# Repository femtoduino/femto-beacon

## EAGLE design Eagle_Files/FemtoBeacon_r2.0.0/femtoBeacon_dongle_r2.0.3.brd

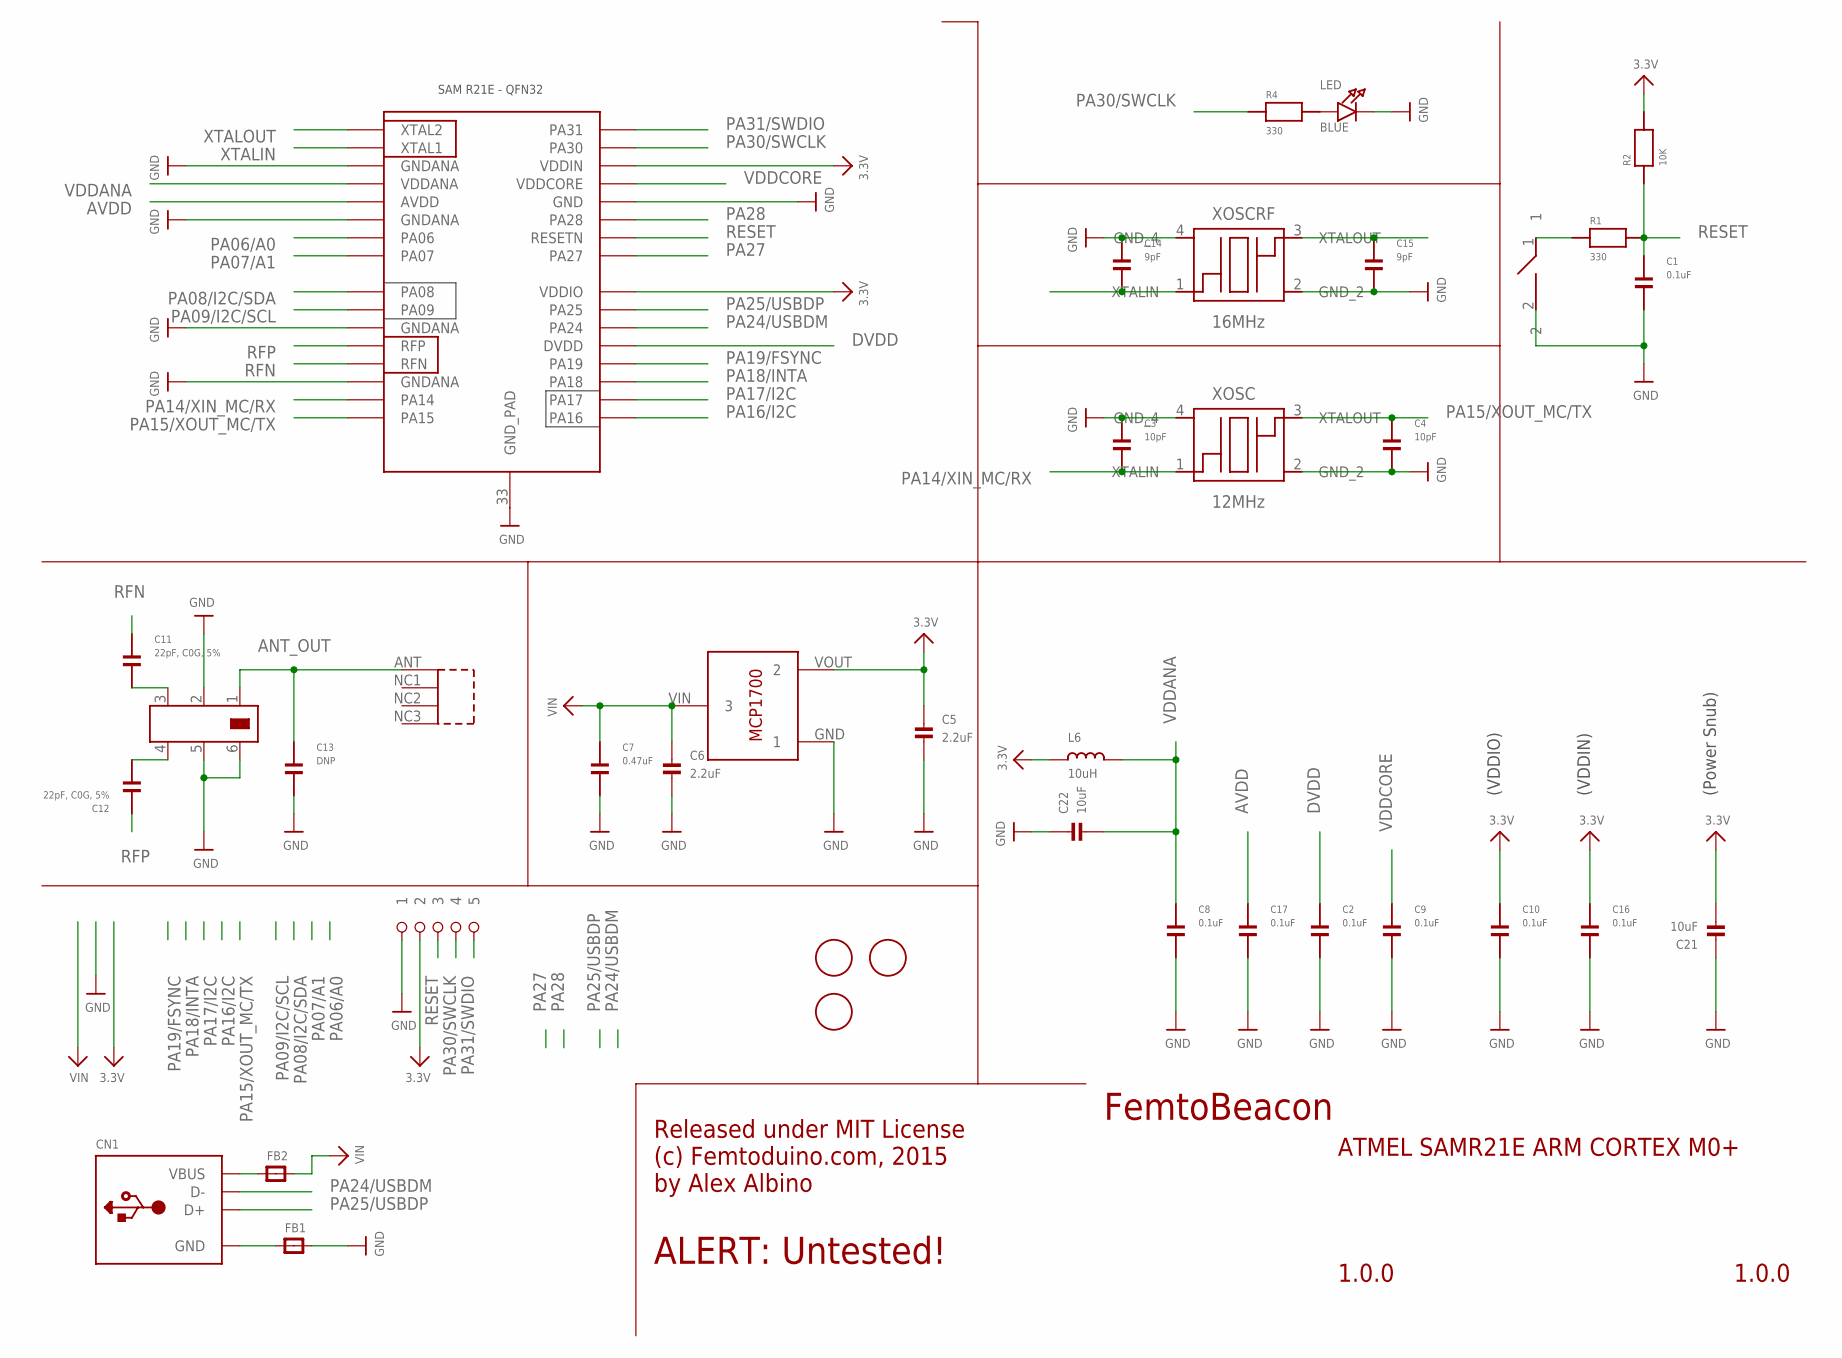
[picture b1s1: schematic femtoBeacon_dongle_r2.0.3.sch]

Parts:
BTN: DNP; SPST_SMD
C1, C8, C9, C10, C16, C17: 0.1uF; PART; DIGIKEY_PART 490-3194-1-ND
C2: 0.1uF; PART
C3, C4: 10pF; PART; DIGIKEY_PART 490-3194-1-ND
C5, C6: 2.2uF; _0402MP
C7: 0.47uF; PART
C11, C12: 22pF, C0G, 5%; PART; DIGIKEY_PART 490-3194-1-ND
C13: DNP; PART; DIGIKEY_PART 490-3194-1-ND
C14, C15: 9pF; PART; DIGIKEY_PART 490-3194-1-ND
C21, C22: 10uF; _0402MP
CN1: USB_TYPEA; USB_A-SMT
FB1, FB2: FERRITE_0603MP; _0603MP
FID1, FID2, FID3: FIDUCIAL; FIDUCIAL_1MM
L6: 10uH; _0603MP
LDO_VREG: MCP1700T-3302E/TT
LED: BLUE; CHIPLED_0603_NOOUTLINE
R1, R4: 330; PART
R2: 10K; PART
U$1: 1X5_ROUND
U$6: 0479480001
U$12: JOHANSON_2450BM15A0015E; 0805_BALUN
U$76: ATSAMR21E18A-MUT; QFN32
XOSC: 12MHz; TSX-3225
XOSCRF: 16MHz; TSX-3225

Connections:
3.3V: C5.1, C10.1, C16.1, C21.2, L6.1, LDO_VREG.VOUT (2), R2.2, U$1.P$2 (2), U$76.24 (VDDIO), U$76.30 (VDDIN)
ANT_OUT: C13.1, U$6.ANT (1), U$12.1
AVDD: C17.1, U$76.5 (AVDD)
DVDD: C2.1, U$76.21 (DVDD)
GND: BTN.2, C1.2, C2.2, C3.1, C4.2, C5.2, C6.2, C7.2, C8.2, C9.2, C10.2, C13.2, C14.1, C15.2, C16.2, C17.2, C21.1, C22.1, FB1.2, LDO_VREG.GND (1), LED.C, U$1.P$1 (1), U$12.2, U$12.5, U$12.6, U$76.3 (GNDANA), U$76.6 (GNDANA), U$76.11 (GNDANA), U$76.14 (GNDANA), U$76.28 (GND), U$76.33 (GND_PAD), XOSC.2 (GND_2), XOSC.4 (GND_4), XOSCRF.2 (GND_2), XOSCRF.4 (GND_4)
unnamed: C11.2, U$12.3
unnamed: C12.2, U$12.4
unnamed: CN1.VBUS, FB2.1
unnamed: CN1.GND, FB1.1
unnamed: LED.A, R4.2
unnamed: BTN.1, R1.1
PA06/A0: U$76.7 (PA06)
PA07/A1: U$76.8 (PA07)
PA08/I2C/SDA: U$76.9 (PA08)
PA09/I2C/SCL: U$76.10 (PA09)
PA14/XIN_MC/RX: C3.2, U$76.15 (PA14), XOSC.1 (XTALIN)
PA15/XOUT_MC/TX: C4.1, U$76.16 (PA15), XOSC.3 (XTALOUT)
PA16/I2C: U$76.17 (PA16)
PA17/I2C: U$76.18 (PA17)
PA18/INTA: U$76.19 (PA18)
PA19/FSYNC: U$76.20 (PA19)
PA24/USBDM: CN1.D-, U$76.22 (PA24)
PA25/USBDP: CN1.D+, U$76.23 (PA25)
PA27: U$76.25 (PA27)
PA28: U$76.27 (PA28)
PA30/SWCLK: R4.1, U$1.P$4 (4), U$76.31 (PA30)
PA31/SWDIO: U$1.P$5 (5), U$76.32 (PA31)
RESET: C1.1, R1.2, R2.1, U$1.P$3 (3), U$76.26 (RESETN)
RFN: C11.1, U$76.13 (RFN)
RFP: C12.1, U$76.12 (RFP)
VDDANA: C8.1, C22.2, L6.2, U$76.4 (VDDANA)
VDDCORE: C9.1, U$76.29 (VDDCORE)
VIN: C6.1, C7.1, FB2.2, LDO_VREG.VIN (3)
XTALIN: C14.2, U$76.2 (XTAL1), XOSCRF.1 (XTALIN)
XTALOUT: C15.1, U$76.1 (XTAL2), XOSCRF.3 (XTALOUT)

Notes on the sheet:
FemtoBeacon
1.0.0
ATMEL SAMR21E ARM CORTEX M0+
Released under MIT License (c) Femtoduino.com, 2015 by Alex Albino
ALERT: Untested!
(Power Snub)
(VDDIO)
(VDDIN)

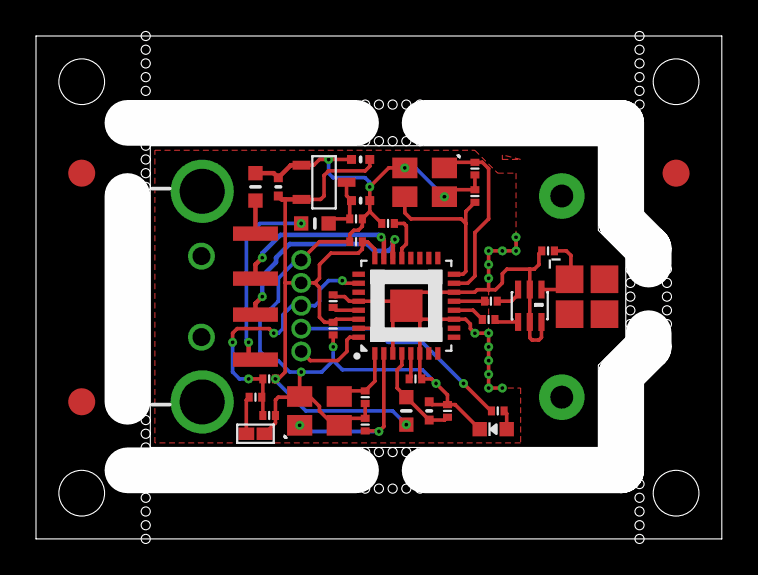
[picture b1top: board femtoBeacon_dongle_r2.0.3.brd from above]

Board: 4 copper layers, 38.1 x 27.9 mm, 38 parts (0 on the bottom side), 25 nets.

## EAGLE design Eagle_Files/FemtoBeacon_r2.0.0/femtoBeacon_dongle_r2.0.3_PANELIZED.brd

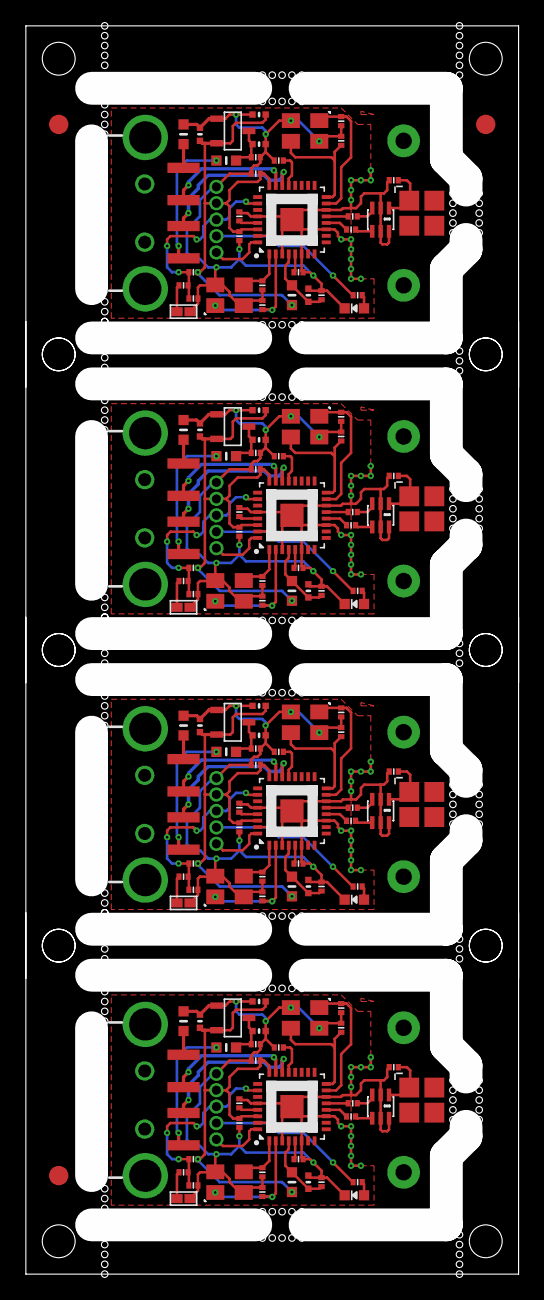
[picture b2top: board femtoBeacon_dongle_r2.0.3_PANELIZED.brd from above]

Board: 4 copper layers, 38.1 x 96.5 mm, 143 parts (0 on the bottom side), 100 nets.

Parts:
BTN, BTN1, BTN2, BTN3: DNP; SPST_SMD
C1, C2, C8, C9, C10, C16, C17, C18, C19, C27, C28, C29, C37, C38, C39, C40, C46, C47, C48, C56, C57, C58, C59, C65, C66, C67, C75, C76: 0.1uF; PART
C3, C4, C32, C33, C51, C52, C70, C71: 10pF; PART
C5, C6, C34, C35, C53, C54, C72, C73: 2.2uF; _0402MP
C7, C36, C55, C74: 0.47uF; PART
C11, C12, C20, C23, C41, C42, C60, C61: 22pF, C0G, 5%; PART
C13, C24, C43, C62: DNP; PART
C14, C15, C25, C26, C44, C45, C63, C64: 9pF; PART
C21, C22, C30, C31, C49, C50, C68, C69: 10uF; _0402MP
CN1, CN2, CN3, CN4: USB_A-SMT
FB1, FB2, FB3, FB4, FB5, FB6, FB7, FB8: _0603MP
FID1, FID2, FID3: FIDUCIAL; FIDUCIAL_1MM
L1, L2, L3, L6: 10uH; _0603MP
LDO_VREG, LDO_VREG1, LDO_VREG2, LDO_VREG3: MCP1700T-3302E/TT
LED, LED1, LED2, LED3: BLUE; CHIPLED_0603_NOOUTLINE
R1, R3, R4, R6, R7, R9, R10, R12: 330; PART
R2, R5, R8, R11: 10K; PART
U$1, U$4, U$9, U$14: 1X5_ROUND
U$2, U$7, U$11, U$12: JOHANSON_2450BM15A0015E; 0805_BALUN
U$3, U$8, U$13, U$76: ATSAMR21E18A-MUT; QFN32
U$5, U$6, U$10, U$15: 0479480001
XOSC, XOSC1, XOSC2, XOSC3: 12MHz; TSX-3225
XOSCRF, XOSCRF1, XOSCRF2, XOSCRF3: 16MHz; TSX-3225

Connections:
3.3V: C5.1, C10.1, C16.1, C21.2, L6.1, LDO_VREG.VOUT, R2.2, U$1.P$2, U$76.24, U$76.30
3.3V1: C19.1, C27.1, C30.2, C34.1, L1.1, LDO_VREG1.VOUT, R5.2, U$3.24, U$3.30, U$4.P$2
3.3V2: C40.1, C46.1, C49.2, C53.1, L2.1, LDO_VREG2.VOUT, R8.2, U$8.24, U$8.30, U$9.P$2
3.3V3: C59.1, C65.1, C68.2, C72.1, L3.1, LDO_VREG3.VOUT, R11.2, U$13.24, U$13.30, U$14.P$2
ANT_OUT: C13.1, U$6.ANT, U$12.1
ANT_OUT1: C24.1, U$2.1, U$5.ANT
ANT_OUT2: C43.1, U$7.1, U$10.ANT
ANT_OUT3: C62.1, U$11.1, U$15.ANT
AVDD: C17.1, U$76.5
AVDD1: C28.1, U$3.5
AVDD2: C47.1, U$8.5
AVDD3: C66.1, U$13.5
DVDD: C2.1, U$76.21
DVDD1: C29.1, U$3.21
DVDD2: C48.1, U$8.21
DVDD3: C67.1, U$13.21
GND: BTN.2, C1.2, C2.2, C3.1, C4.2, C5.2, C6.2, C7.2, C8.2, C9.2, C10.2, C13.2, C14.1, C15.2, C16.2, C17.2, C21.1, C22.1, FB1.2, LDO_VREG.GND, LED.C, U$1.P$1, U$12.2, U$12.5, U$12.6, U$76.3, U$76.6, U$76.11, U$76.14, U$76.28, U$76.33, XOSC.2, XOSC.4, XOSCRF.2, XOSCRF.4
GND1: BTN1.2, C18.2, C19.2, C24.2, C25.1, C26.2, C27.2, C28.2, C29.2, C30.1, C31.1, C32.1, C33.2, C34.2, C35.2, C36.2, C37.2, C38.2, FB3.2, LDO_VREG1.GND, LED1.C, U$2.2, U$2.5, U$2.6, U$3.3, U$3.6, U$3.11, U$3.14, U$3.28, U$3.33, U$4.P$1, XOSC1.2, XOSC1.4, XOSCRF1.2, XOSCRF1.4
GND2: BTN2.2, C39.2, C40.2, C43.2, C44.1, C45.2, C46.2, C47.2, C48.2, C49.1, C50.1, C51.1, C52.2, C53.2, C54.2, C55.2, C56.2, C57.2, FB5.2, LDO_VREG2.GND, LED2.C, U$7.2, U$7.5, U$7.6, U$8.3, U$8.6, U$8.11, U$8.14, U$8.28, U$8.33, U$9.P$1, XOSC2.2, XOSC2.4, XOSCRF2.2, XOSCRF2.4
GND3: BTN3.2, C58.2, C59.2, C62.2, C63.1, C64.2, C65.2, C66.2, C67.2, C68.1, C69.1, C70.1, C71.2, C72.2, C73.2, C74.2, C75.2, C76.2, FB7.2, LDO_VREG3.GND, LED3.C, U$11.2, U$11.5, U$11.6, U$13.3, U$13.6, U$13.11, U$13.14, U$13.28, U$13.33, U$14.P$1, XOSC3.2, XOSC3.4, XOSCRF3.2, XOSCRF3.4
unnamed: C11.2, U$12.3
unnamed: BTN1.1, R3.1
unnamed: C12.2, U$12.4
unnamed: CN1.VBUS, FB2.1
unnamed: CN1.GND, FB1.1
unnamed: LED1.A, R6.2
unnamed: C20.2, U$2.3
unnamed: C23.2, U$2.4
unnamed: LED.A, R4.2
unnamed: CN2.GND, FB3.1
unnamed: CN2.VBUS, FB4.1
unnamed: BTN2.1, R7.1
unnamed: LED2.A, R9.2
unnamed: C41.2, U$7.3
unnamed: C42.2, U$7.4
unnamed: CN3.GND, FB5.1
unnamed: CN3.VBUS, FB6.1
unnamed: BTN.1, R1.1
unnamed: BTN3.1, R10.1
unnamed: LED3.A, R12.2
unnamed: C60.2, U$11.3
unnamed: C61.2, U$11.4
unnamed: CN4.GND, FB7.1
unnamed: CN4.VBUS, FB8.1
PA14/XIN_MC/RX: C3.2, U$76.15, XOSC.1
PA14/XIN_MC/RX1: C32.2, U$3.15, XOSC1.1
PA14/XIN_MC/RX2: C51.2, U$8.15, XOSC2.1
PA14/XIN_MC/RX3: C70.2, U$13.15, XOSC3.1
PA15/XOUT_MC/TX: C4.1, U$76.16, XOSC.3
PA15/XOUT_MC/TX1: C33.1, U$3.16, XOSC1.3
PA15/XOUT_MC/TX2: C52.1, U$8.16, XOSC2.3
PA15/XOUT_MC/TX3: C71.1, U$13.16, XOSC3.3
PA24/USBDM: CN1.D-, U$76.22
PA24/USBDM1: CN2.D-, U$3.22
PA24/USBDM2: CN3.D-, U$8.22
PA24/USBDM3: CN4.D-, U$13.22
PA25/USBDP: CN1.D+, U$76.23
PA25/USBDP1: CN2.D+, U$3.23
PA25/USBDP2: CN3.D+, U$8.23
PA25/USBDP3: CN4.D+, U$13.23
PA30/SWCLK: R4.1, U$1.P$4, U$76.31
PA30/SWCLK1: R6.1, U$3.31, U$4.P$4
PA30/SWCLK2: R9.1, U$8.31, U$9.P$4
PA30/SWCLK3: R12.1, U$13.31, U$14.P$4
PA31/SWDIO: U$1.P$5, U$76.32
PA31/SWDIO1: U$3.32, U$4.P$5
PA31/SWDIO2: U$8.32, U$9.P$5
PA31/SWDIO3: U$13.32, U$14.P$5
RESET: C1.1, R1.2, R2.1, U$1.P$3, U$76.26
RESET1: C18.1, R3.2, R5.1, U$3.26, U$4.P$3
RESET2: C39.1, R7.2, R8.1, U$8.26, U$9.P$3
RESET3: C58.1, R10.2, R11.1, U$13.26, U$14.P$3
RFN: C11.1, U$76.13
RFN1: C20.1, U$3.13
RFN2: C41.1, U$8.13
RFN3: C60.1, U$13.13
RFP: C12.1, U$76.12
RFP1: C23.1, U$3.12
RFP2: C42.1, U$8.12
RFP3: C61.1, U$13.12
VDDANA: C8.1, C22.2, L6.2, U$76.4
VDDANA1: C31.2, C37.1, L1.2, U$3.4
VDDANA2: C50.2, C56.1, L2.2, U$8.4
VDDANA3: C69.2, C75.1, L3.2, U$13.4
VDDCORE: C9.1, U$76.29
VDDCORE1: C38.1, U$3.29
VDDCORE2: C57.1, U$8.29
VDDCORE3: C76.1, U$13.29
VIN: C6.1, C7.1, FB2.2, LDO_VREG.VIN
VIN1: C35.1, C36.1, FB4.2, LDO_VREG1.VIN
VIN2: C54.1, C55.1, FB6.2, LDO_VREG2.VIN
VIN3: C73.1, C74.1, FB8.2, LDO_VREG3.VIN
XTALIN: C14.2, U$76.2, XOSCRF.1
XTALIN1: C25.2, U$3.2, XOSCRF1.1
XTALIN2: C44.2, U$8.2, XOSCRF2.1
XTALIN3: C63.2, U$13.2, XOSCRF3.1
XTALOUT: C15.1, U$76.1, XOSCRF.3
XTALOUT1: C26.1, U$3.1, XOSCRF1.3
XTALOUT2: C45.1, U$8.1, XOSCRF2.3
XTALOUT3: C64.1, U$13.1, XOSCRF3.3

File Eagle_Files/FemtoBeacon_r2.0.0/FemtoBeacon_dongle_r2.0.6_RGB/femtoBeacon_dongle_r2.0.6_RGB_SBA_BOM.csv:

##########################################################################
       Name: Placement Bill of Materials Generator

    Version: 4 (2-sided, top)
         By: Small Batch Assembly
        URL: www.smallbatchassembly.com
 SourceFile: femtoBeacon_dongle_r2.0.6_RGB.brd
   DateTime: 1/3/18 4:22 AM
      Units: inches
##########################################################################
REF,PACKAGE,VALUE,X,Y,ROTATION,
ASWITCH   , AS222-92LF            , AS222-92LF     , 1.1500, 0.5100, 0.0
BTN   , SPST_SMD            , DNP     , 0.4800, 0.2300, 0.0
C1   , PART            , 0.1uF     , 0.5100, 0.2700, 0.0
C2   , PART            , 0.1uF     , 0.7700, 0.6900, 180.0
C5   , _0402MP            , 2.2uF     , 0.7100, 0.8300, 180.0
C6   , _0402MP            , 2.2uF     , 0.7100, 0.7400, 0.0
C7   , PART            , 0.47uF     , 0.7000, 0.7000, 0.0
C8   , PART            , 0.1uF     , 0.9000, 0.2800, 90.0
C9   , PART            , 0.1uF     , 0.6500, 0.5200, 90.0
C10   , PART            , 0.1uF     , 0.7000, 0.6500, 180.0
C11   , _0402MP            , 1.2pF     , 1.2300, 0.6000, 180.0
C13   , PART            , DNP     , 1.1100, 0.6600, 180.0
C14   , PART            , 9pF     , 0.7200, 0.2500, 270.0
C15   , PART            , 9pF     , 0.7200, 0.3100, 270.0
C16   , PART            , 0.1uF     , 0.6500, 0.4600, 270.0
C17   , PART            , 0.1uF     , 0.8300, 0.3500, 0.0
C18   , PART            , 22pF     , 1.1500, 0.5900, 270.0
C19   , PART            , 22pF     , 1.1800, 0.5900, 270.0
C20   , PART            , 22pF     , 1.1200, 0.5900, 90.0
C21   , _0402MP            , 10uF     , 0.5300, 0.7700, 270.0
C22   , _0402MP            , 10uF     , 0.8600, 0.2800, 270.0
C23   , PART            , 22pF     , 1.1760, 0.3980, 90.0
C24   , PART            , 22pF     , 1.2400, 0.5400, 90.0
CN1   , USB_A-SMT            ,      , 0.4800, 0.5300, 90.0
FB1   , _0603MP            ,      , 0.4800, 0.7700, 90.0
FB2   , _0603MP            ,      , 0.6100, 0.6900, 0.0
FID1   , FIDUCIAL_1MM            , FIDUCIAL     , 0.1000, 0.3000, 0.0
FID2   , FIDUCIAL_1MM            , FIDUCIAL     , 0.1000, 0.8000, 0.0
FID3   , FIDUCIAL_1MM            , FIDUCIAL     , 1.4500, 0.8000, 0.0
L1   , _0603MP            , 1.8nH     , 1.2060, 0.6560, 0.0
L6   , _0603MP            , 10uH     , 0.8100, 0.2800, 90.0
LDO_VREG   , MCP1700T-3302E/TT            , MCP1700T-3302E/TT     , 0.6300, 0.7800, 270.0
R1   , PART            , 330     , 0.4800, 0.3100, 0.0
R2   , PART            , 10K     , 0.5100, 0.3500, 0.0
R4   , PART            , 330     , 0.9700, 0.2600, 0.0
R6   , PART            , 330     , 0.9700, 0.3000, 0.0
R7   , PART            , 330     , 0.9800, 0.3480, 0.0
RGBLED   , LRTB_R48G            , LRTB_R48G     , 1.0300, 0.2800, 270.0
U$6   , 0479480001            , 0479480001     , 1.2040, 0.7770, 90.0
U$12   , 0805_BALUN            , JOHANSON_2450BM15A0015E     , 1.0500, 0.5100, 270.0
U$76   , QFN32            , ATSAMR21E18A-MUT     , 0.8100, 0.5100, 90.0
UFLANT   , U.FL            , uFL     , 1.1860, 0.2900, 90.0
XOSCRF   , TSX-3225            , 16MHz     , 0.6200, 0.2800, 0.0

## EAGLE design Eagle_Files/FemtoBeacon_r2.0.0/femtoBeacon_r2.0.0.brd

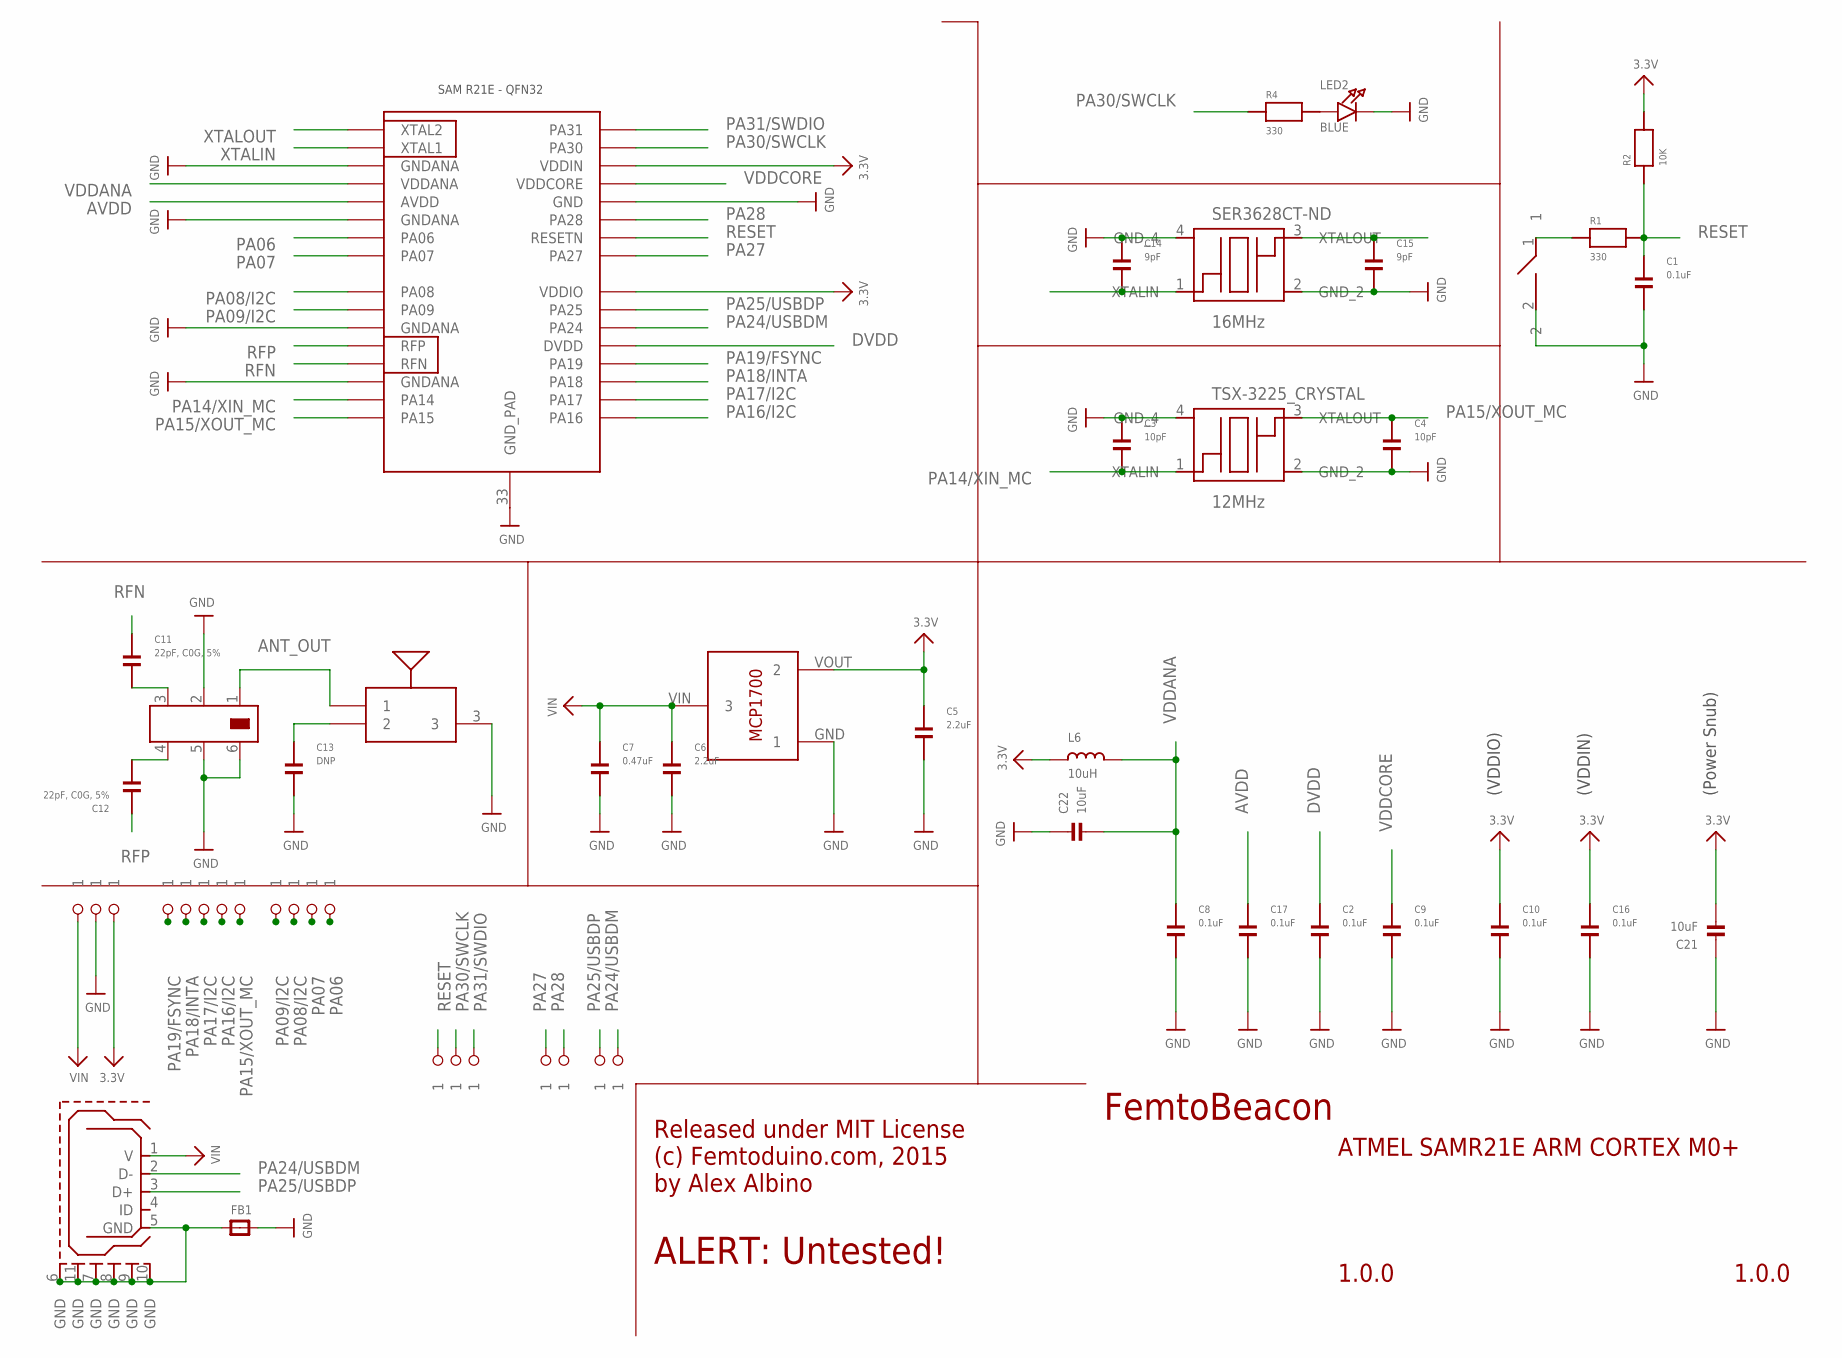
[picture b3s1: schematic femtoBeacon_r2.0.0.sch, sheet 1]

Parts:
ANT1: PULSE_ANT_2.4GHZ; ANT_BAR
BTN: DNP; SPST_SMD
C1, C8, C9, C10, C16, C17: 0.1uF; PART; DIGIKEY_PART 490-3194-1-ND
C2: 0.1uF; PART
C3, C4: 10pF; PART; DIGIKEY_PART 490-3194-1-ND
C5, C6: 2.2uF; PART
C7: 0.47uF; PART
C11, C12: 22pF, C0G, 5%; PART; DIGIKEY_PART 490-3194-1-ND
C13: DNP; PART; DIGIKEY_PART 490-3194-1-ND
C14, C15: 9pF; PART; DIGIKEY_PART 490-3194-1-ND
C21, C22: 10uF; _0402MP
FB1: FERRITE_0603MP; _0603MP
L6: 10uH; _0603MP
LDO_VREG: MCP1700T-3302E/TT
LED2: BLUE; CHIPLED_0603_NOOUTLINE
R1, R4: 330; PART
R2: 10K; PART
SER3628CT-ND: 16MHz; TSX-3225
TSX-3225_CRYSTAL: 12MHz; TSX-3225
U$1, U$2, U$5, U$7, U$9, U$10, U$35, U$36, U$37, U$38, U$39, U$41, U$42, U$43, U$45, U$46, U$47, U$48, U$54: 1X1_ROUND
U$12: JOHANSON_2450BM15A0015E; 0805_BALUN
U$76: ATSAMR21E18A-MUT; QFN32
USB: USB_MICROB; USB_MICROB_PACKAGE

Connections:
3.3V: C5.1, C10.1, C16.1, C21.2, L6.1, LDO_VREG.VOUT (2), R2.2, U$5.P$1, U$76.24 (VDDIO), U$76.30 (VDDIN); also elsewhere on the board
ANT_OUT: ANT1.1, U$12.1
AVDD: C17.1, U$76.5 (AVDD)
DVDD: C2.1, U$76.21 (DVDD)
GND: ANT1.3, BTN.2, C1.2, C2.2, C3.1, C4.2, C5.2, C6.2, C7.2, C8.2, C9.2, C10.2, C13.2, C14.1, C15.2, C16.2, C17.2, C21.1, C22.1, FB1.2, LDO_VREG.GND (1), LED2.C, SER3628CT-ND.2 (GND_2), SER3628CT-ND.4 (GND_4), TSX-3225_CRYSTAL.2 (GND_2), TSX-3225_CRYSTAL.4 (GND_4), U$2.P$1, U$12.2, U$12.5, U$12.6, U$76.3 (GNDANA), U$76.6 (GNDANA), U$76.11 (GNDANA), U$76.14 (GNDANA), U$76.28 (GND), U$76.33 (GND_PAD); also elsewhere on the board
unnamed: C11.2, U$12.3
unnamed: ANT1.2, C13.1
unnamed: C12.2, U$12.4
unnamed: FB1.1, USB.5 (GND), USB.6 (GND), USB.7 (GND), USB.8 (GND), USB.9 (GND), USB.10 (GND), USB.11 (GND)
unnamed: LED2.A, R4.2
unnamed: BTN.1, R1.1
PA06: U$54.P$1, U$76.7 (PA06)
PA07: U$43.P$1, U$76.8 (PA07)
PA08/I2C: U$42.P$1, U$76.9 (PA08); also elsewhere on the board
PA09/I2C: U$41.P$1, U$76.10 (PA09); also elsewhere on the board
PA14/XIN_MC: C3.2, TSX-3225_CRYSTAL.1 (XTALIN), U$76.15 (PA14)
PA15/XOUT_MC: C4.1, TSX-3225_CRYSTAL.3 (XTALOUT), U$39.P$1, U$76.16 (PA15)
PA16/I2C: U$38.P$1, U$76.17 (PA16)
PA17/I2C: U$37.P$1, U$76.18 (PA17)
PA18/INTA: U$36.P$1, U$76.19 (PA18); also elsewhere on the board
PA19/FSYNC: U$35.P$1, U$76.20 (PA19); also elsewhere on the board
PA24/USBDM: U$9.P$1, U$76.22 (PA24), USB.2 (D-)
PA25/USBDP: U$10.P$1, U$76.23 (PA25), USB.3 (D+)
PA27: U$7.P$1, U$76.25 (PA27)
PA28: U$48.P$1, U$76.27 (PA28)
PA30/SWCLK: R4.1, U$46.P$1, U$76.31 (PA30)
PA31/SWDIO: U$47.P$1, U$76.32 (PA31)
RESET: C1.1, R1.2, R2.1, U$45.P$1, U$76.26 (RESETN)
RFN: C11.1, U$76.13 (RFN)
RFP: C12.1, U$76.12 (RFP)
VDDANA: C8.1, C22.2, L6.2, U$76.4 (VDDANA)
VDDCORE: C9.1, U$76.29 (VDDCORE)
VIN: C6.1, C7.1, LDO_VREG.VIN (3), U$1.P$1, USB.1 (V)
XTALIN: C14.2, SER3628CT-ND.1 (XTALIN), U$76.2 (XTAL1)
XTALOUT: C15.1, SER3628CT-ND.3 (XTALOUT), U$76.1 (XTAL2)

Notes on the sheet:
FemtoBeacon
1.0.0
ATMEL SAMR21E ARM CORTEX M0+
Released under MIT License (c) Femtoduino.com, 2015 by Alex Albino
ALERT: Untested!
(Power Snub)
(VDDIO)
(VDDIN)

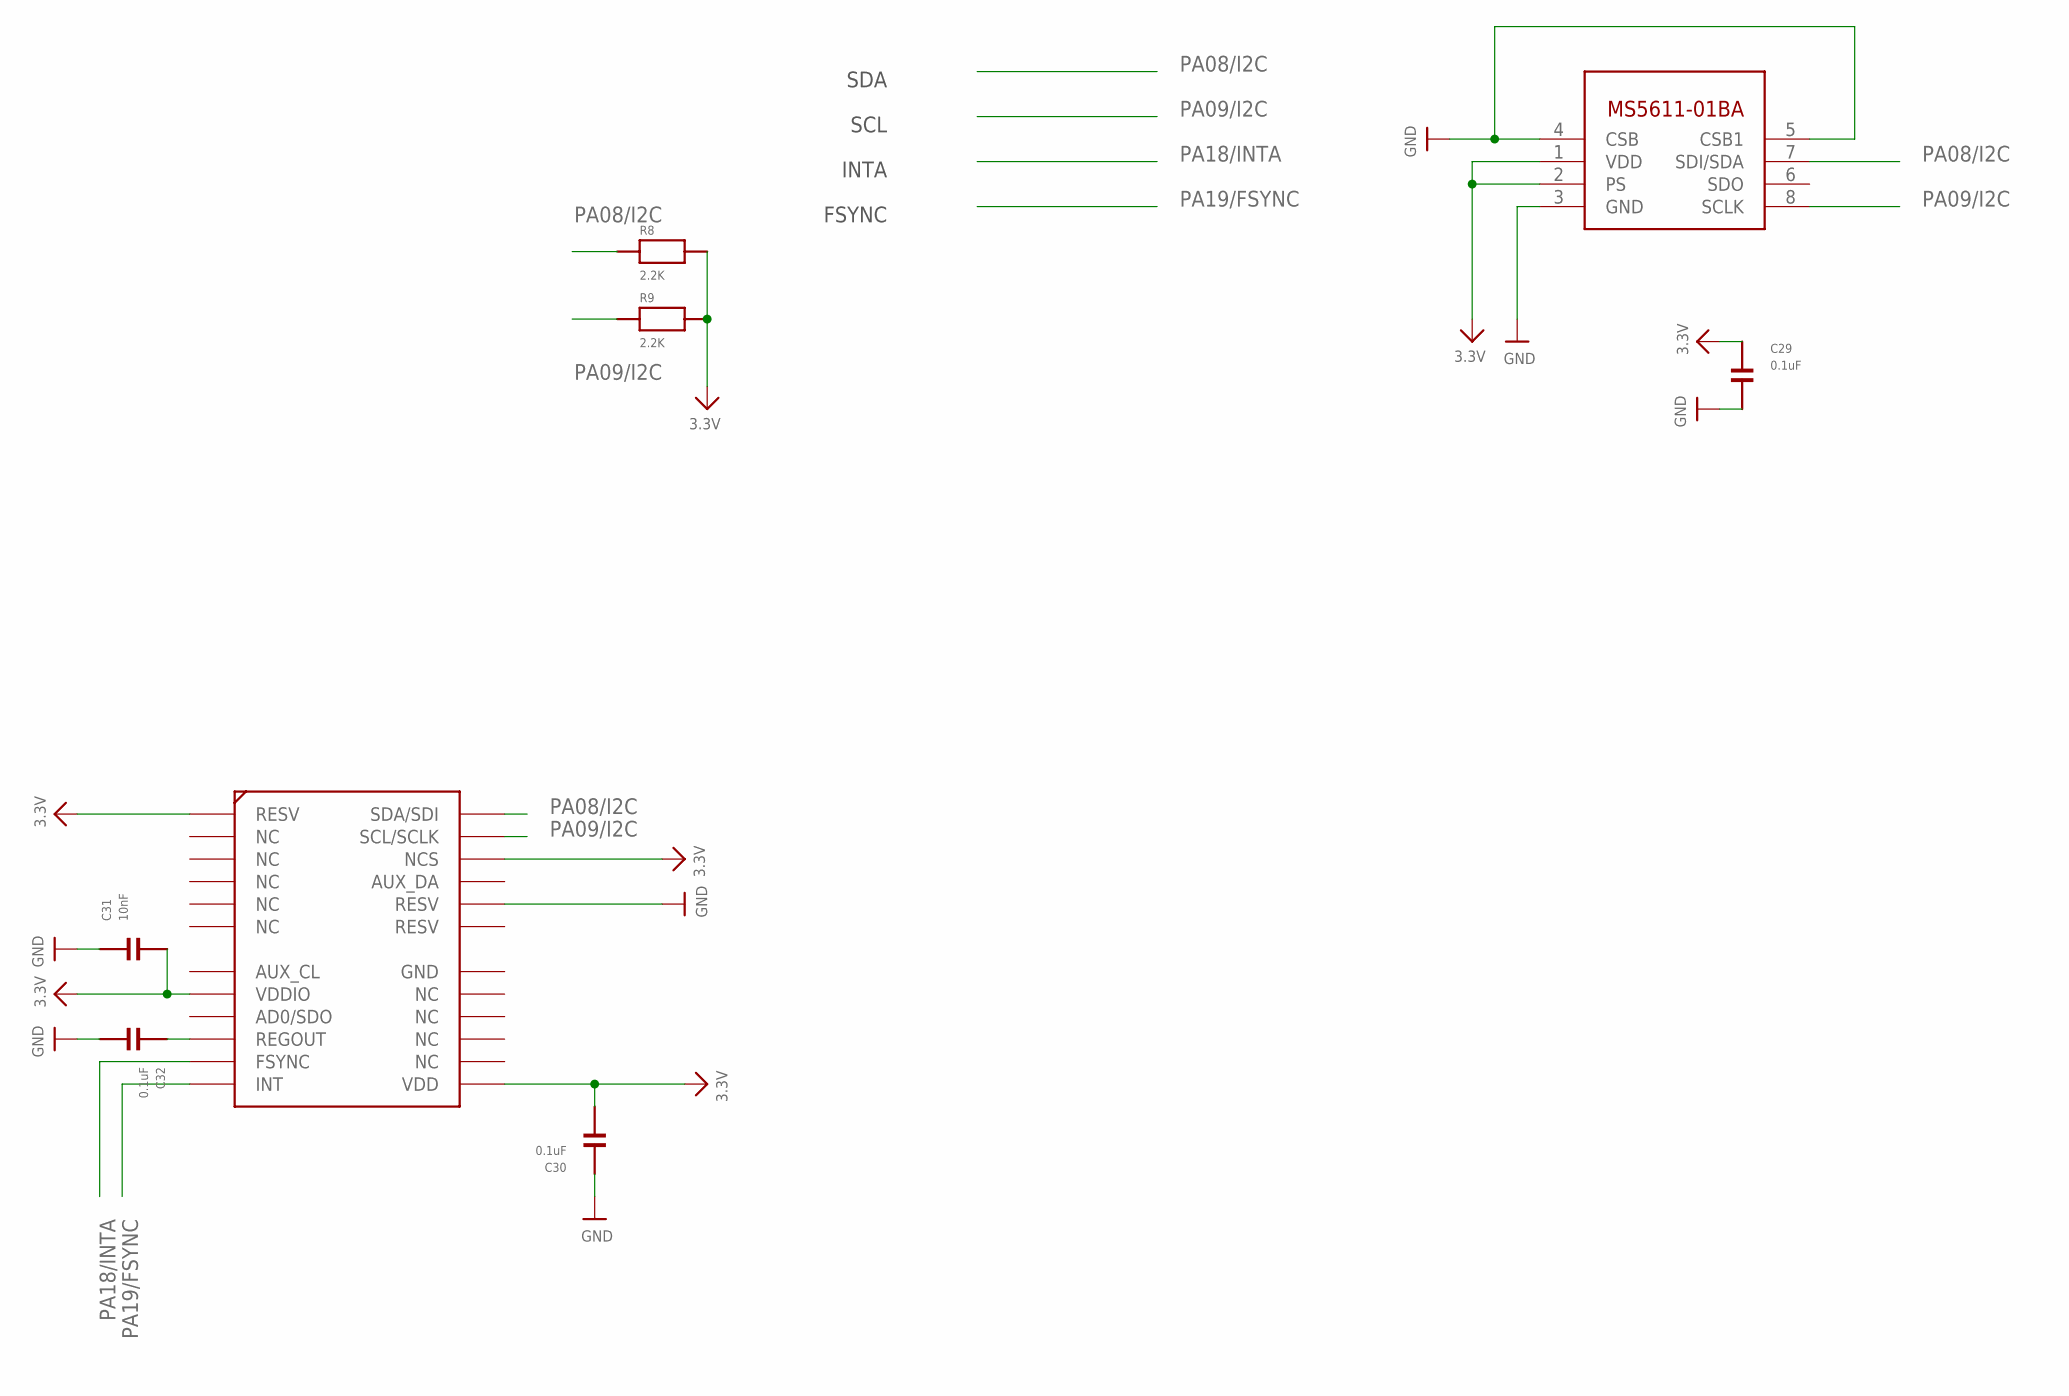
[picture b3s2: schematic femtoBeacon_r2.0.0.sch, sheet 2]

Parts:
C29, C30, C32: 0.1uF; PART; DIGIKEY_PART 490-3194-1-ND
C31: 10nF; PART; DIGIKEY_PART 490-3194-1-ND
R8, R9: 2.2K; PART
U$6: MPU-9250; QFN_3X3MM
U$44: MS5611-01BA03

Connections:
3.3V: C29.1, C30.2, C31.2, R8.2, R9.2, U$6.P$1 (RESV), U$6.P$8 (VDDIO), U$6.P$13 (VDD), U$6.P$22 (NCS), U$44.1 (VDD), U$44.2 (PS); also elsewhere on the board
GND: C29.2, C30.1, C31.1, C32.2, U$6.P$20 (RESV), U$44.3 (GND), U$44.4 (CSB), U$44.5 (CSB1); also elsewhere on the board
unnamed: C32.1, U$6.P$10 (REGOUT)
PA08/I2C: R8.1, U$6.P$24 (SDA/SDI), U$44.7 (SDI/SDA); also elsewhere on the board
PA09/I2C: R9.1, U$6.P$23 (SCL/SCLK), U$44.8 (SCLK); also elsewhere on the board
PA18/INTA: U$6.P$11 (FSYNC); also elsewhere on the board
PA19/FSYNC: U$6.P$12 (INT); also elsewhere on the board

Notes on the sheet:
SDA
SCL
INTA
FSYNC

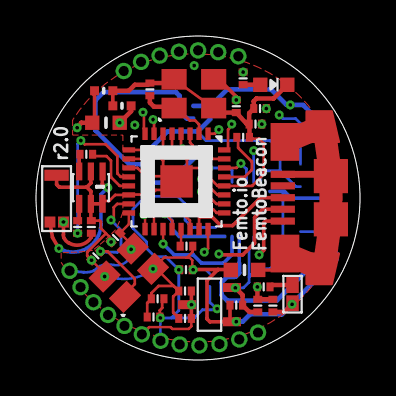
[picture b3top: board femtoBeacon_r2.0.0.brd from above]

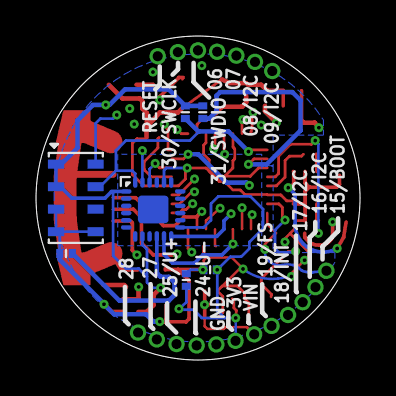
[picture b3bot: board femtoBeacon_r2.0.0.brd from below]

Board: 4 copper layers, 18.0 x 18.0 mm, 60 parts (7 on the bottom side), 36 nets.

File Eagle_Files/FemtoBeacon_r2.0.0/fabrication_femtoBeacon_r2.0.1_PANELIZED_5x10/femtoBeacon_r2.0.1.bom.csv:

"Qty","Value","Device","Package","Parts","Description","DIGIKEY_PART"
"1",,"FERRITE_0603MP","_0603MP","FB1","Ferrite Bead",
"10","0.1uF","CAPACITOR_0201","PART","C1, C2, C8, C9, C10, C16, C17, C29, C30, C32",,"490-3194-1-ND"
"1","0.47uF","CAPACITOR_0201","PART","C7",,
"1","10K","RESISTOR_0201","PART","R2",,
"1","10nF","CAPACITOR_0201","PART","C31",,"490-3194-1-ND"
"2","10pF","CAPACITOR_0201","PART","C3, C4",,"490-3194-1-ND"
"2","10uF","CAP_CERAMIC_0402MP","_0402MP","C21, C22","Ceramic Capacitors",
"1","10uH","INDUCTOR_0603MP","_0603MP","L6","Inductors",
"1","12MHz","TSX-3225","TSX-3225","XOSC",,
"1","16MHz","TSX-3225","TSX-3225","XOSCRF",,
"2","2.2K","RESISTOR_0201","PART","R8, R9",,
"2","2.2uF","CAP_CERAMIC_0402MP","_0402MP","C5, C6","Ceramic Capacitors",
"2","22pF, C0G, 5%","CAPACITOR_0201","PART","C11, C12",,"490-3194-1-ND"
"2","330","RESISTOR_0201","PART","R1, R4",,
"2","9pF","CAPACITOR_0201","PART","C14, C15",,"490-3194-1-ND"
"1","ATSAMR21E18A-MUT","ATSAMR21E18A-MUT","QFN32","IC","This is the ATMEL SAMR21E QFN-32. ATSAMR21E18A",
"1","BLUE","LED0603_NOOUTLINE","CHIPLED_0603_NOOUTLINE","LED2","LED",
"1","JOHANSON_2450BM15A0015E","JOHANSON_2450BM15A0015E","0805_BALUN","BAL",,
"1","MCP1700T-3302E/TT","MCP1700T-3302E/TT","MCP1700T-3302E/TT","LDO_VREG","Microchip LDO ""MCP1700"" in a 3-Pin SOT-23 package.",
"1","MPU-9250","MPU-9250","QFN_3X3MM","IMU",,
"1","MS5611-01BA03","MS5611-01BA03","MS5611-01BA03","BARO",,
"1","PULSE_ANT_2.4GHZ","PULSE_ANT_2.4GHZ","ANT_BAR","ANT1","Manufacturer part #W3008",
"1","USB_MICROB","USB_MICROB","USB_MICROB_PACKAGE","USB","This is the hirose ZX62-B-5PA(11) MICRO-USB B Type female connection.",

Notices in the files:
parts and their libraries:
microbuilder: This work is placed in the public domain, and may be freely used for commercial and non-commercial work with the following conditions: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
